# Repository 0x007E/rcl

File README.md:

# `RCL` - RGB Color Lamp

The `RCL` is a board with a set of [APA102](#additional-information) or any other `SPI` controllable `RGB-LED`. The board itself is driven with `5V` over USB and can be configured with the integrated UART interface ([MCP2221A](#additional-information)). The `Color Lamp` itself is controlled over the additional `Touchpad` ([TPD](https://github.com/0x007e/tpd/)) and can be switched on/off over a slide switch.

| Experience  | Level                                                                               |
|:------------|:-----------------------------------------------------------------------------------:|
| Soldering   |  |
| Mechanical  |  |

# Downloads

| Type      | File                                                                                                                                                 | Description     |
|:---------:|:----------------------------------------------------------------------------------------------------------------------------------------------------:|:----------------|
| Schematic | [pdf](https://github.com/0x007E/rcl/releases/latest/download/schematic.pdf) / [cadlab](https://cadlab.io/project/30341/main/files)                   | Schematic files |
| Board     | [pdf](https://github.com/0x007E/rcl/releases/latest/download/pcb.pdf) / [cadlab](https://cadlab.io/project/30341/main/files)                         | Board file      |
| Drill     | [pdf](https://github.com/0x007E/rcl/releases/latest/download/drill.pdf)                                                                              | Drill file      |
| BoM | [xlsx](https://github.com/0x007E/rcl/releases/latest/download/bom.xlsx) / [html](https://github.com/0x007E/rcl/releases/latest/download/bom.html)          | Bill of Material as Excel/interactive HTML |
| PCB    | [zip](https://github.com/0x007E/rcl/releases/latest/download/kicad.zip) / [tar](https://github.com/0x007E/rcl/releases/latest/download/kicad.tar.gz)    | KiCAD/Gerber/BoM/Drill files       |
| Mechanical | [zip](https://github.com/0x007E/rcl/releases/latest/download/freecad.zip) / [tar](https://github.com/0x007E/rcl/releases/latest/download/freecad.tar.gz) | FreeCAD/Housing and PCB (STEP/STL) files     |

# Hardware

The pcb is created with `KiCAD`, the housing with `FreeCAD`. All files are built with `github actions` so that they are ready for a production environment.

## PCB

The circuit board is populated on both sides (Top, Bottom). The best way for soldering the `SMD` components is within a vapor phase soldering system and for the `THT` components with a standard soldering system.

### Top Layer

### Bottom Layer

## Mechanical

The housing has a tolerance of `0.2mm` on each side of the case. So the pcb should fit perfectly in the housing. The tolerance can be modified with `FreeCAD` in the `Parameter` Spreadsheet.

### Assembled

### Exploded

# Additional Information

| Type       | Link                                                                                                      | Description                                        |
|:----------:|:---------------------------------------------------------------------------------------------------------:|:---------------------------------------------------|
| APA102     | [pdf](https://cdn.sparkfun.com/datasheets/Components/LED/APA102C.pdf)                                     | RGB Full Color LED                                 |
| T3A33BRG   | [pdf](https://mm.digikey.com/Volume0/opasdata/d220001/medias/docus/6794/3147_T3A33BRG-H9C0002X1U1930.pdf) | Harvatek Surface Mount PLCC IC+RGB LEDs Data Sheet |
| MCP2221A   | [pdf](https://ww1.microchip.com/downloads/en/devicedoc/20005565b.pdf)                                     | USB 2.0 to I2C/UART Protocol Converter with GPIO   |

---

R. GAECHTER

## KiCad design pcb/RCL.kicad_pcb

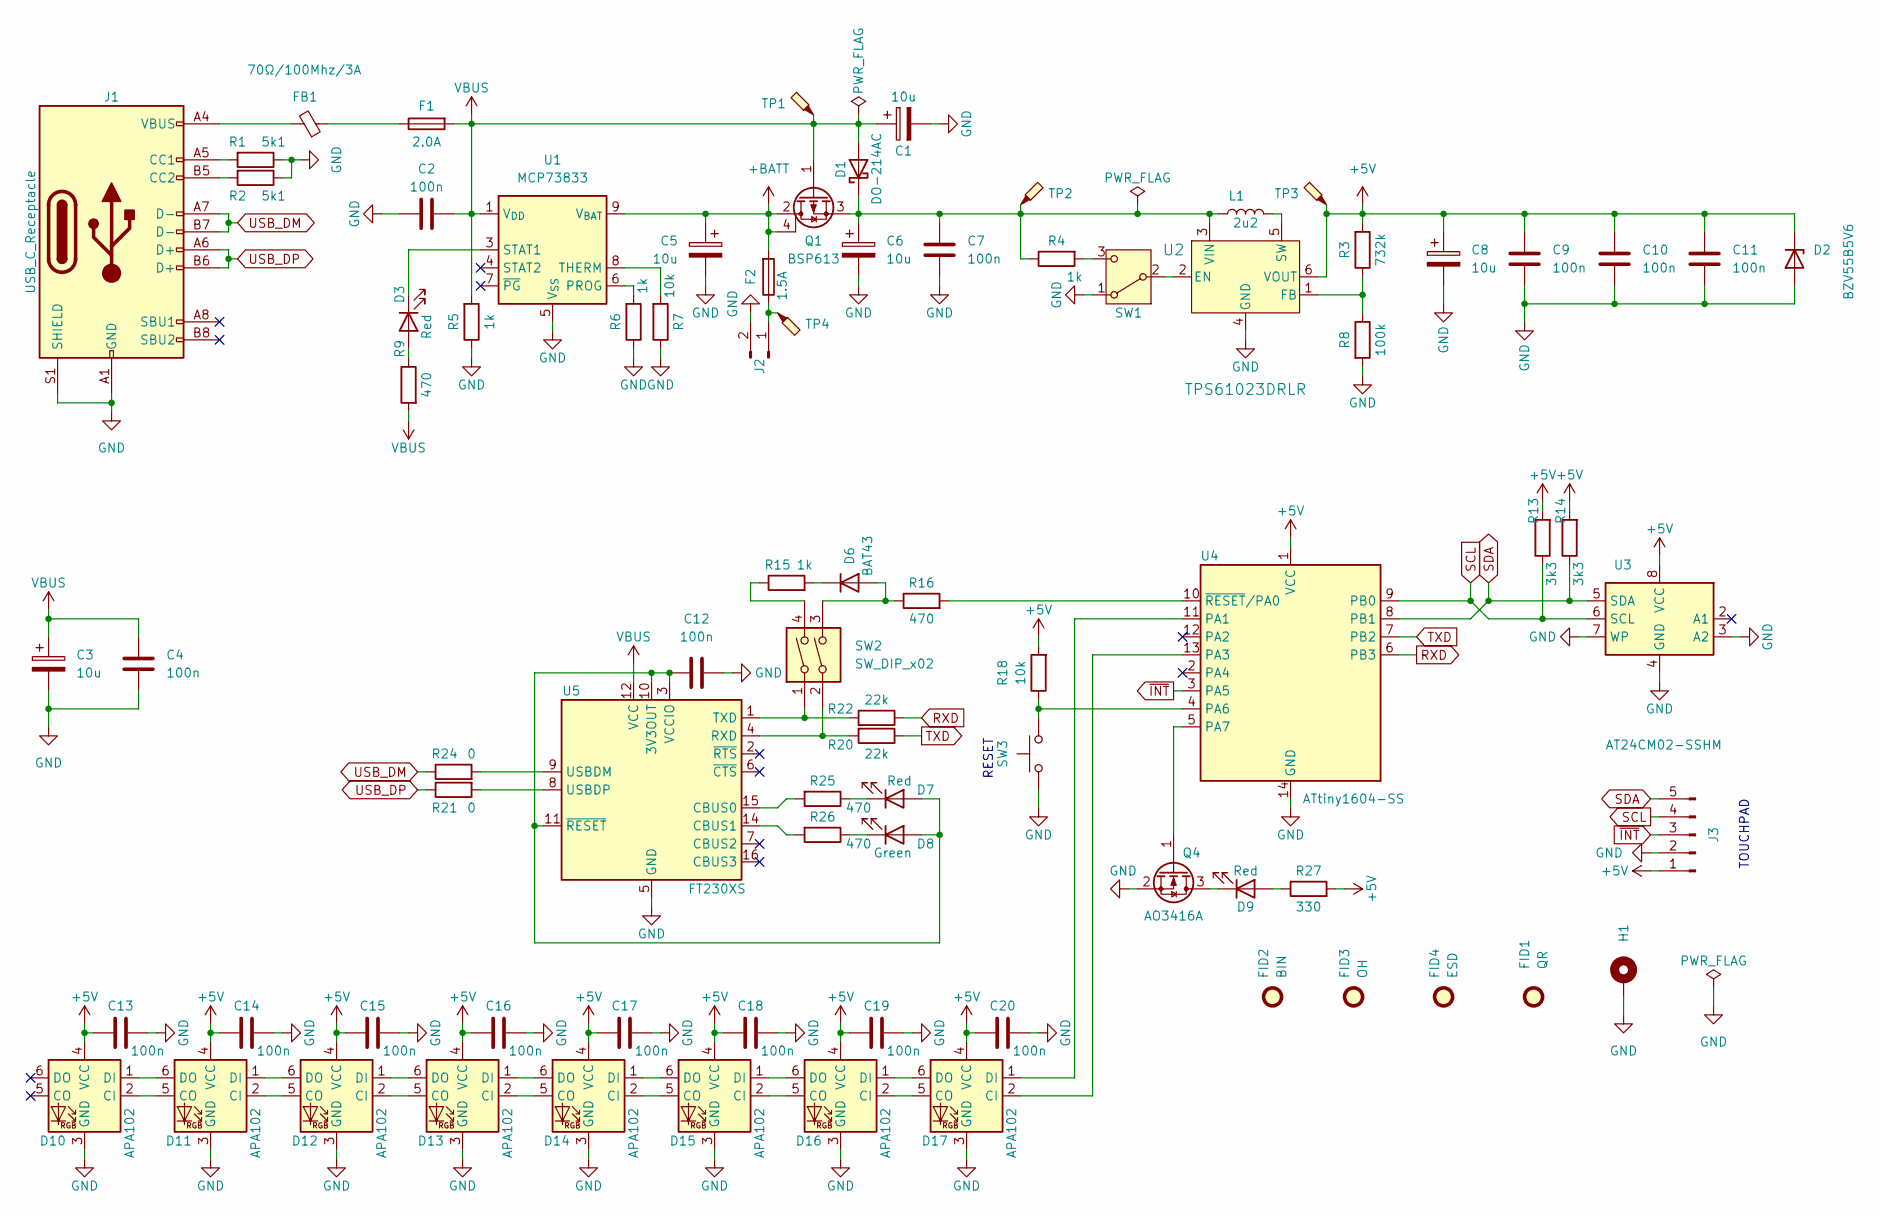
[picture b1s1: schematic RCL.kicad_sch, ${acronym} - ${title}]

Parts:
C1, C5, C6, C8: 10u; CP_EIA-6032-28_Kemet-C
C2, C4, C7, C9, C10, C11, C12, C13, C14, C15, C16, C17, C18, C19, C20: 100n; C_1206_3216Metric
C3: 10u; CP_EIA-3528-21_Kemet-B
D1: DO-214AC; D_SMA
D2: BZV55B5V6; D_MiniMELF
D3, D7, D9: Red; LED_1206_3216Metric
D6: BAT43; D_MiniMELF
D8: Green; LED_1206_3216Metric
D10, D11, D12, D13, D14, D15, D16, D17: APA102; LED_RGB_5050-6
F1: 2.0A; Fuse_1206_3216Metric
F2: 1.5A; Fuse_1206_3216Metric
FB1: 70Ω/100Mhz/3A; L_1206_3216Metric
FID1: QR; QR_0x007e_very_small
FID2: BIN; WEEE-Logo_4.2x6mm_SilkScreen
FID3: OH; OSHW-Logo2_7.3x6mm_SilkScreen
FID4: ESD; ESD-Logo_6.6x6mm_SilkScreen
H1: MountingHole_Pad; MountingHole_3.2mm_M3_DIN965_Pad
J1: USB_C_Receptacle; USB_C_Receptacle_GCT_USB4110
J2: Conn_01x02_Pin; JST_PH_S2B-PH-K_1x02_P2.00mm_Horizontal; DigiKey BC2AAAW-ND, 455-2266-ND, BXH-001T-P0.6-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
J3: Conn_01x05_Pin; PinSocket_1x05_P2.54mm_Vertical
L1: 2u2; L_Vishay_IFSC-1515AH_4x4x1.8mm
Q1: BSP613; SOT-223
Q4: AO3416A; SOT-23
R1, R2: 5k1; R_1206_3216Metric
R3: 732k; R_1206_3216Metric
R4, R5, R6, R15: 1k; R_1206_3216Metric
R7, R18: 10k; R_1206_3216Metric
R8: 100k; R_1206_3216Metric
R9, R16, R25, R26: 470; R_1206_3216Metric
R13, R14: 3k3; R_1206_3216Metric
R20, R22: 22k; R_1206_3216Metric
R21, R24: 0; R_0603_1608Metric; DigiKey RMCF0603ZT0R00CT-ND
R27: 330; R_1206_3216Metric
SW1: SW_SPDT; SW_SPDT_CK_JS102011SAQN
SW2: SW_DIP_x02; SW_DIP_SPSTx02_Slide_6.7x6.64mm_W8.61mm_P2.54mm_LowProfile
SW3: SW_Push; SW_SPST_PTS645
TP1, TP2, TP3, TP4: TestPoint_Probe; TestPoint_Pad_D1.0mm
U1: MCP73833; MSOP-10_3x3mm_P0.5mm
U2: TPS61023DRLR; SOT-563
U3: AT24CM02-SSHM; SOIC-8_3.9x4.9mm_P1.27mm
U4: ATtiny1604-SS; SOIC-14_3.9x8.7mm_P1.27mm
U5: FT230XS; SSOP-16_3.9x4.9mm_P0.635mm

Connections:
+5V: C8.1, C9.1, C10.1, C11.1, C13.2, C14.2, C15.2, C16.2, C17.2, C18.2, C19.2, C20.2, D2.1 (K), D10.4 (VCC), D11.4 (VCC), D12.4 (VCC), D13.4 (VCC), D14.4 (VCC), D15.4 (VCC), D16.4 (VCC), D17.4 (VCC), J3.1, R3.2, R13.2, R14.2, R18.2, R27.2, TP3.1, U2.6 (VOUT), U3.8 (VCC), U4.1 (VCC)
+BATT: C5.1, F2.2, Q1.2 (D), Q1.4 (D), U1.9 (V_{BAT}), U1.10 (V_{BAT})
GND: C1.2, C2.2, C3.2, C4.2, C5.2, C6.2, C7.2, C8.2, C9.2, C10.2, C11.2, C12.2, C13.1, C14.1, C15.1, C16.1, C17.1, C18.1, C19.1, C20.1, D2.2 (A), D10.3 (GND), D11.3 (GND), D12.3 (GND), D13.3 (GND), D14.3 (GND), D15.3 (GND), D16.3 (GND), D17.3 (GND), H1.1, J1.A1 (GND), J1.A12 (GND), J1.B1 (GND), J1.B12 (GND), J1.S1 (SHIELD), J2.2, J3.2, Q4.2 (S), R1.1, R2.1, R5.1, R6.1, R7.1, R8.2, SW1.1 (A), SW3.1, U1.5 (V_{SS}), U2.4 (GND), U3.3 (A2), U3.4 (GND), U3.7 (WP), U4.14 (GND), U5.5 (GND), U5.13 (GND)
unnamed: C6.1, C7.1, D1.1 (K), L1.1, Q1.3 (S), R4.1, TP2.1, U2.3 (VIN)
unnamed: D3.2 (A), R9.1
unnamed: D3.1 (K), U1.3 (STAT1)
unnamed: D6.2 (A), R16.1, SW2.3
unnamed: D6.1 (K), R15.2
unnamed: C12.1, D7.2 (A), D8.2 (A), U5.3 (VCCIO), U5.10 (3V3OUT), U5.11 (~RESET)
unnamed: D7.1 (K), R25.1
unnamed: D8.1 (K), R26.1
unnamed: D9.2 (A), R27.1
unnamed: D9.1 (K), Q4.3 (D)
unnamed: D10.2 (CI), D11.5 (CO)
unnamed: D10.1 (DI), D11.6 (DO)
unnamed: D11.2 (CI), D12.5 (CO)
unnamed: D11.1 (DI), D12.6 (DO)
unnamed: D12.2 (CI), D13.5 (CO)
unnamed: D12.1 (DI), D13.6 (DO)
unnamed: D13.2 (CI), D14.5 (CO)
unnamed: D13.1 (DI), D14.6 (DO)
unnamed: D14.2 (CI), D15.5 (CO)
unnamed: D14.1 (DI), D15.6 (DO)
unnamed: D15.2 (CI), D16.5 (CO)
unnamed: D15.1 (DI), D16.6 (DO)
unnamed: D16.2 (CI), D17.5 (CO)
unnamed: D16.1 (DI), D17.6 (DO)
unnamed: D17.2 (CI), U4.13 (PA3)
unnamed: D17.1 (DI), U4.11 (PA1)
unnamed: F1.1, FB1.1
unnamed: FB1.2, J1.A4 (VBUS), J1.A9 (VBUS), J1.B4 (VBUS), J1.B9 (VBUS)
unnamed: J1.A5 (CC1), R1.2
unnamed: J1.B5 (CC2), R2.2
unnamed: F2.1, J2.1, TP4.1
unnamed: Q4.1 (G), U4.5 (PA7)
unnamed: R15.1, SW2.4
unnamed: SW1.2 (B), U2.2 (EN)
unnamed: R4.2, SW1.3 (C)
unnamed: R6.2, U1.6 (PROG)
unnamed: R7.2, U1.8 (THERM)
unnamed: R3.1, R8.1, U2.1 (FB)
unnamed: L1.2, U2.5 (SW)
unnamed: R18.1, SW3.2, U4.4 (PA6)
unnamed: R16.2, U4.10 (~RESET/PA0)
unnamed: R25.2, U5.15 (CBUS0)
unnamed: R26.2, U5.14 (CBUS1)
unnamed: R20.2, SW2.2, U5.4 (RXD)
unnamed: R22.2, SW2.1, U5.1 (TXD)
unnamed: R24.2, U5.9 (USBDM)
unnamed: R21.2, U5.8 (USBDP)
RXD: R22.1, U4.6 (PB3)
SCL: J3.4, R13.1, U3.6 (SCL), U4.9 (PB0)
SDA: J3.5, R14.1, U3.5 (SDA), U4.8 (PB1)
TXD: R20.1, U4.7 (PB2)
USB_DM: J1.A7 (D-), J1.B7 (D-), R24.1
USB_DP: J1.A6 (D+), J1.B6 (D+), R21.1
VBUS: C1.1, C2.1, C3.1, C4.1, D1.2 (A), F1.2, Q1.1 (G), R5.2, R9.2, TP1.1, U1.1 (V_{DD}), U1.2 (V_{DD}), U5.12 (VCC)
~INT: J3.3, U4.3 (PA5)

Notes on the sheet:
TOUCHPAD
RESET

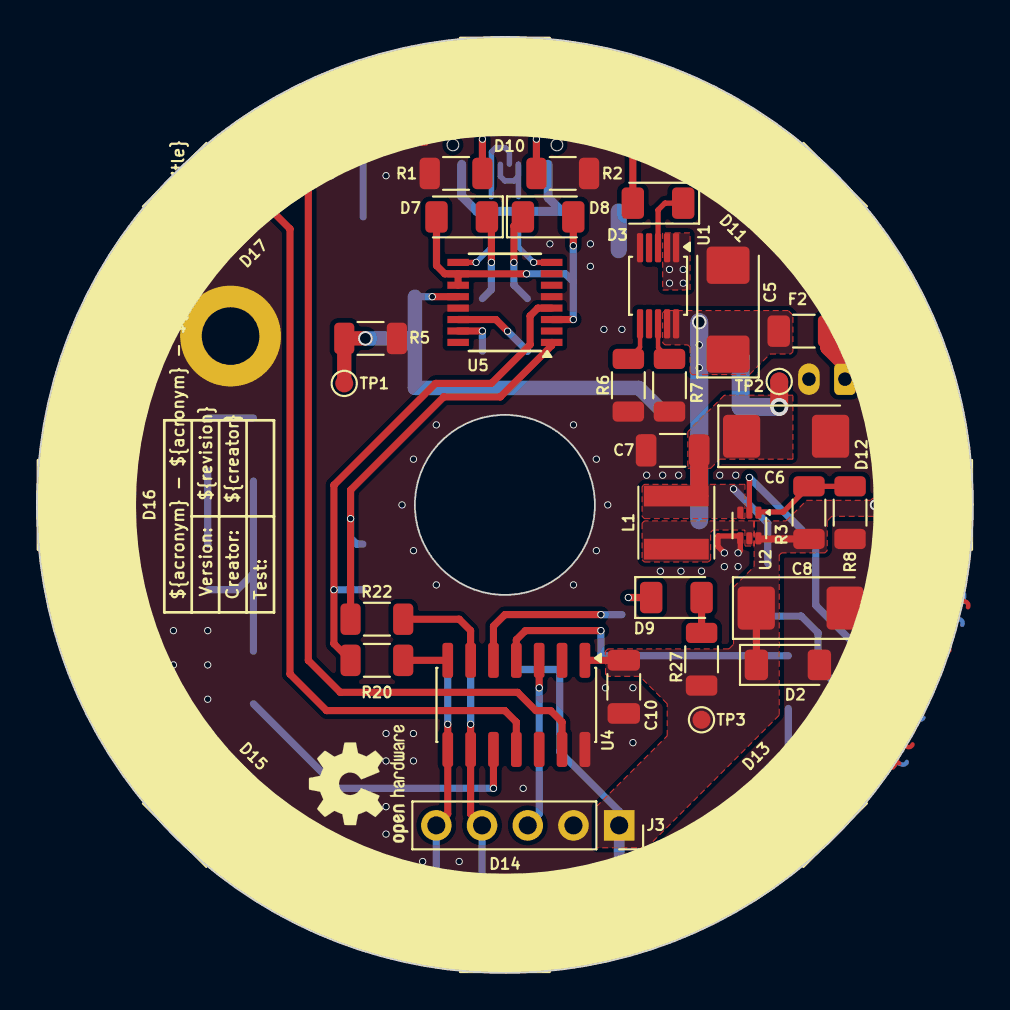
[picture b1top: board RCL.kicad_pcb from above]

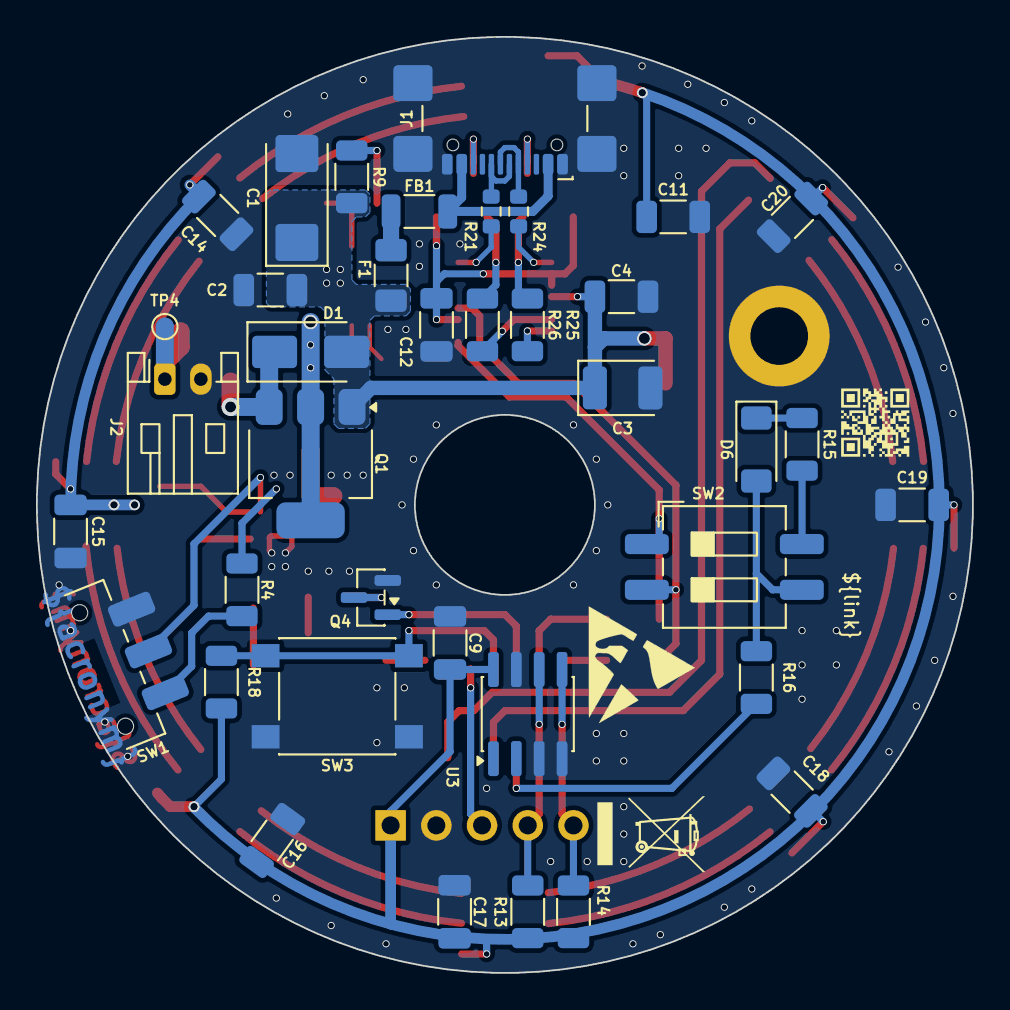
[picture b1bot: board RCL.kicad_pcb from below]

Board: 2 copper layers, 52.0 x 52.0 mm, 82 parts (41 on the bottom side), 58 nets.

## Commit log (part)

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2026-05-14 Move pcb position on sheet
2026-05-14 Optimize fabrication layer
2026-05-14 Optimize parameter properties
2026-05-22 Add missing vendor(id)
2026-05-27 Text smoothing
2026-05-27 Rename/Add/Remove bom fields
2026-05-27 Optimize/Extend release pipeline
2026-05-29 Fix wrong urls in download section
2026-06-04 Change MCP2221A to FT230X
2026-06-05 Optimize +3V3 signal

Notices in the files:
README.md:
License CC By-NC-SA
parts and their libraries:
license: CC BY-NC-SA 4.0
